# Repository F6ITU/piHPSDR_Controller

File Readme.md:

'''PiHPSDR, a embedded SDR controler for the OpenHPSDR Software Defined Radio familly'''

This repository is a "pseudo fork" of a Raspberry Pi based SDR controler created by Kjell Karlsen LA2NI and Laurence Baker G8NJJ
for the hardware project, and by John Melton G0ORX for the software part.

The original software repository could be found at https://github.com/g0orx/pihpsdr 

The whole KiCAD design effort has been made by Matthis Schmieder, DB9MAT https://github.com/mathisschmieder. May he be thanked for the quality of his work 
 
His schematic is in fact a simplified version or G0ORX's project (https://github.com/g0orx/pihpsdr/blob/master/controller/PiHPSDR_Controller_MK_II_Rev.2_Schema.zip), 
using single axis encoders instead hard to find dual axis devices. 

Assembly instructions -in French language- could be found on the Electrolab's Wiki https://wiki.electrolab.fr/Projets:Lab:2020:PiHPSDR

This very simple Ham Radio project is perfect for beginners who intend to beginners strengthen their experience in the SMD field.
 
 An interactive BOM could be downloaded from the BOM directory (iBom Pihpsdr controler.html), and a complete Excel spreadsheet 
 gives the references of each component used, using mostly the Mouser catalog

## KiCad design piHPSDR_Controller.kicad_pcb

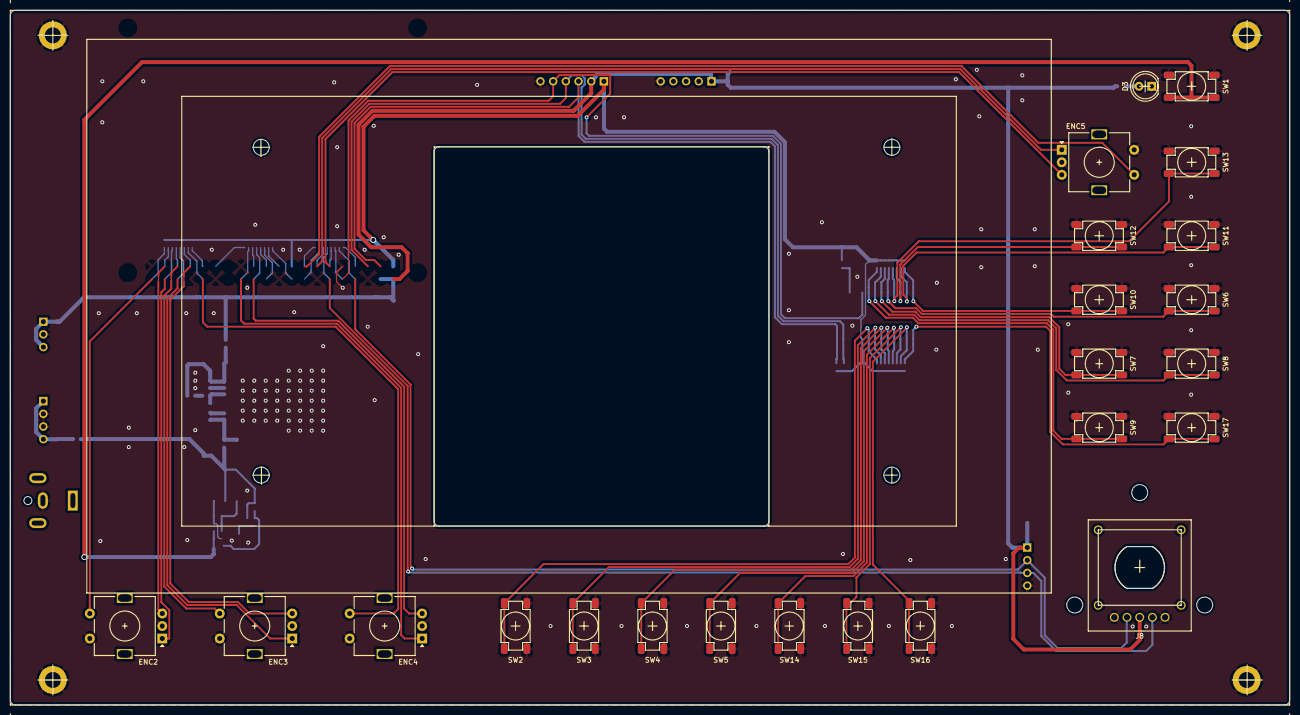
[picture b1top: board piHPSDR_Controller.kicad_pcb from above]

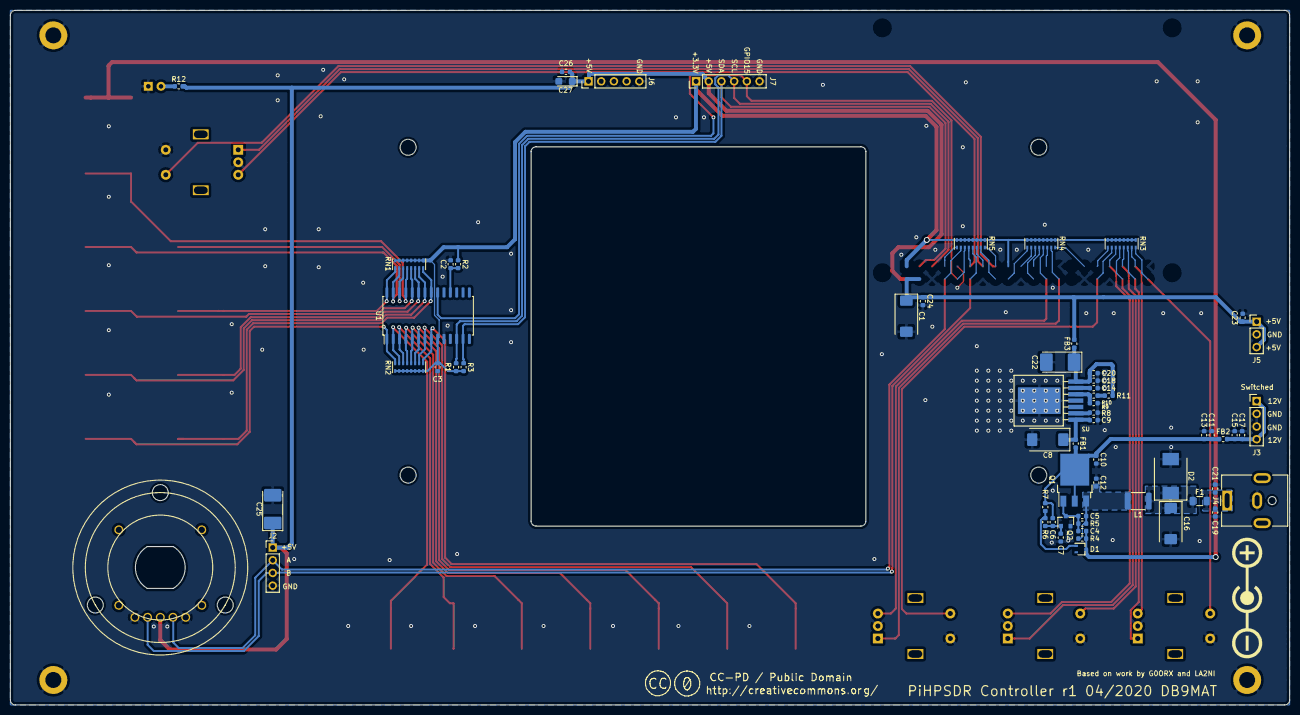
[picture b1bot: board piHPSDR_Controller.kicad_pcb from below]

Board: 2 copper layers, 256.0 x 139.0 mm, 88 parts (61 on the bottom side), 53 nets.

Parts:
 : MountingHole_3.2mm_M3_DIN965_Pad
 #2,  #3,  #4: MountingHole_3.2mm_M3_DIN965_Pad
C1: 220u/10V; CP_EIA-7343-31_Kemet-D
C2: 1n; C_0603_1608Metric
C3, C10, C12, C20, C21, C24, C26: 10u; C_0603_1608Metric
C4, C13, C17: 1u; C_0603_1608Metric
C5, C6, C7, C9, C11, C14, C15, C18, C19, C23: 100n; C_0603_1608Metric
C8: 47u/35V; CP_EIA-7343-43_Kemet-X
C16: 22u/35V; CP_EIA-7343-31_Kemet-D
C22, C25: 100u/10V; CP_EIA-7132-28_AVX-C
C27: 100u/6.3V; CP_EIA-3216-18_Kemet-A
D1: BAS16J; SOT-323_SC-70
D2: SK54; D_SMC
D3: Green; LED_D5.0mm
ENC2, ENC3, ENC4, ENC5: Rotary_Encoder_Switch; RotaryEncoder_Alps_EC11E-Switch_Vertical_H20mm
F1: 5A; Fuse_1206_3216Metric
FB1, FB2, FB3: TBD; L_0603_1608Metric
J2: ENC1; PinHeader_1x04_P2.54mm_Vertical
J3: 12V_SWITCHED; PinHeader_1x04_P2.54mm_Vertical
J4: 12V_IN; BarrelJack_CUI_PJ-063AH_Horizontal
J5: 5V/3A; PinHeader_1x03_P2.54mm_Vertical
J6: TO_DISPLAY; PinHeader_1x05_P2.54mm_Vertical
J7: Conn_01x06; PinHeader_1x06_P2.54mm_Vertical
J8: ENC1a; HRPG-AXXX
L1: 74279226101; L_1812_4532Metric
Q1: FDD6685; TO-252-3_TabPin2
Q2: 2N7002K; SOT-23
R1, R3, R4: 10k; R_0603_1608Metric
R2, R5, R7: 100k; R_0603_1608Metric
R6: 180k; R_0603_1608Metric
R8, R12: 1k5; R_0603_1608Metric
R9: 620; R_0603_1608Metric
R10: 3k3; R_0603_1608Metric
R11: 47; R_0603_1608Metric
RN1, RN2, RN3, RN4, RN5: 10k; R_Cat16-8
SW1: ON_OFF; TL3301AF160QG
SW2, SW3, SW4, SW5, SW6, SW7, SW8, SW9, SW10, SW11, SW12, SW13, SW14, SW15, SW16, SW17: SW_Push; TL3301AF160QG
U1: MCP23017_SO; SOIC-28W_7.5x17.9mm_P1.27mm
U2: LMZ22005; 7TO-PMOD

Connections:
+3V3: C3.1, J7.1, R1.2, R2.1, R3.1, RN1.1, RN2.1, RN3.1, RN4.1, RN5.1, U1.9
+5V: C1.1, C23.1, C24.1, C25.1, C26.1, C27.1, FB3.2, J2.1, J5.1, J5.3, J6.1, J7.2, J8.3, R12.2
+12V: C6.1, C10.1, C11.1, C13.1, FB1.2, FB2.2, Q1.2, R7.1
/Raspberry Pi/GPIO2: J7.3, R3.2, U1.13
/Raspberry Pi/GPIO3: J7.4, R1.1, U1.12
GND: .1, #2.1, #3.1, #4.1, C1.2, C2.2, C3.2, C7.2, C8.2, C9.2, C10.2, C11.2, C12.2, C13.2, C14.2, C15.2, C16.2, C17.2, C18.2, C19.2, C20.2, C21.2, C22.2, C23.2, C24.2, C25.2, C26.2, C27.2, D2.2, D3.1, ENC2.C, ENC2.S2, ENC3.C, ENC3.S2, ENC4.C, ENC4.S2, ENC5.C, ENC5.S2, J2.4, J3.2, J3.3, J4.2, J5.2, J6.5, J7.6, J8.1, J8.5, Q2.2, R8.1, R9.1, SW1.1, SW2.1, SW3.1, SW4.1, SW5.1, SW6.1, SW7.1, SW8.1, SW9.1, SW10.1, SW11.1, SW12.1, SW13.1, SW14.1, SW15.1, SW16.1, SW17.1, U1.10, U2.4, U2.8
GPA0: RN1.2, SW9.2, U1.21
GPA1: RN1.3, SW8.2, U1.22
GPA2: RN1.4, SW7.2, U1.23
GPA3: RN1.5, SW6.2, U1.24
GPA4: RN1.6, SW13.2, U1.25
GPA5: RN1.7, SW12.2, U1.26
GPA6: RN1.8, SW11.2, U1.27
GPA7: RN1.9, SW10.2, U1.28
GPB0: RN2.2, SW17.2, U1.1
GPB1: RN2.3, SW16.2, U1.2
GPB2: RN2.4, SW15.2, U1.3
GPB3: RN2.5, SW14.2, U1.4
GPB4: RN2.6, SW5.2, U1.5
GPB5: RN2.7, SW4.2, U1.6
GPB6: RN2.8, SW3.2, U1.7
GPB7: RN2.9, SW2.2, U1.8
GPIO7: ENC4.A, RN4.3
GPIO8: ENC4.B, RN4.5
GPIO12: ENC4.S1, RN3.8
GPIO13: ENC3.B, RN3.7
GPIO14: J2.2, J8.4, RN5.8
GPIO15: J7.5, RN5.7, U1.20
GPIO16: ENC3.A, RN3.6
GPIO17: ENC5.B, RN5.6
GPIO18: J2.3, J8.2, RN5.5
GPIO19: ENC3.S1, RN3.5
GPIO20: ENC2.A, RN3.4
GPIO21: ENC2.S1, RN3.2
GPIO22: ENC5.S1, RN5.2
GPIO26: ENC2.B, RN3.3
GPIO27: ENC5.A, RN5.4
unnamed: C2.1, R2.2, U1.18
unnamed: C4.1, C5.2, Q1.1, Q2.3, R5.2
unnamed: C4.2, D1.3, R4.2, SW1.2
unnamed: C6.2, C7.1, Q2.1, R6.2
unnamed: C8.1, C9.1, FB1.1, U2.1
unnamed: C5.1, C12.1, L1.1, Q1.3, R4.1, R5.1
unnamed: C14.1, U2.6
unnamed: C15.1, C17.1, FB2.1, J3.1, J3.4
unnamed: C16.1, D2.1, F1.1, L1.2
unnamed: C18.1, C20.1, C22.1, FB3.1, R11.2, U2.7
unnamed: C19.1, C21.1, F1.2, J4.1
unnamed: D1.1, R6.1, R7.2
unnamed: D3.2, R12.1
unnamed: R8.2, U2.2
unnamed: R9.2, R10.1, U2.5
unnamed: R10.2, R11.1

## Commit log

2020-07-22 pihpsdr KiCAD board
